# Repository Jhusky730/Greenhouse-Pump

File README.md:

# Greenhouse-Pump

This project is an extention project to my previous project:https://github.com/Jhusky730/solar-greenhouse-monitor

I was inspired to make this as i wanted to have my sensor automatically water my greenhouse for me.

This will be housed within the case for the previous project.
## Flow of current
### 5V
- The 5V current flows from the USB VBUS pads on the previous project to the new pcb. It is soldered onto a solder pad.
- The current flows into a 1x2 screw terminal attached to a 5V Peristaltic Pump.
- The current flows back from the pump into the screw terminal.
- There is a flyback diode to prevent feedback from turning off the pump.
- The current flows into the drain of an N-channel MOSFET.
- If the MOSFET is open the current returns through a solder pad to the other PCB to complete the circuit.
### Logic (3V3)

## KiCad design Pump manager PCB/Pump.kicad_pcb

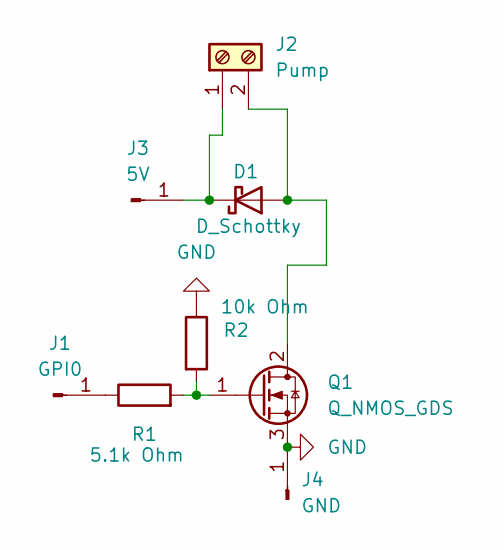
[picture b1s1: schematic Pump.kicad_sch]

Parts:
D1: D_Schottky; D_SMA
J1: GPI0; SolderWire-0.5sqmm_1x01_D0.9mm_OD2.1mm
J2: Pump; TerminalBlock_Phoenix_MKDS-1,5-2-5.08_1x02_P5.08mm_Horizont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
J3: 5V; SolderWire-0.5sqmm_1x01_D0.9mm_OD2.1mm
J4: GND; SolderWire-0.5sqmm_1x01_D0.9mm_OD2.1mm
Q1: Q_NMOS_GDS; SOT-23
R1: 5.1k Ohm; R_0805_2012Metric
R2: 10k Ohm; R_0805_2012Metric

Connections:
GND: J4.1 (Pin_1_1), Q1.3 (S), R2.1
unnamed: D1.2 (A), J2.2, Q1.2 (D)
unnamed: D1.1 (K), J2.1, J3.1 (Pin_1_1)
unnamed: J1.1 (Pin_1_1), R1.1
unnamed: Q1.1 (G), R1.2, R2.2

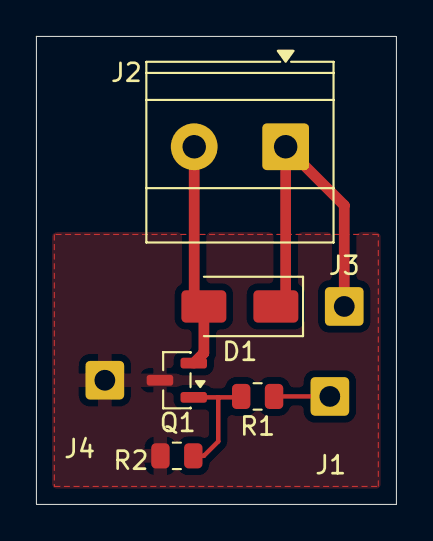
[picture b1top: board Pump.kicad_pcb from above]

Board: 2 copper layers, 20.0 x 26.0 mm, 8 parts (0 on the bottom side), 5 nets.
